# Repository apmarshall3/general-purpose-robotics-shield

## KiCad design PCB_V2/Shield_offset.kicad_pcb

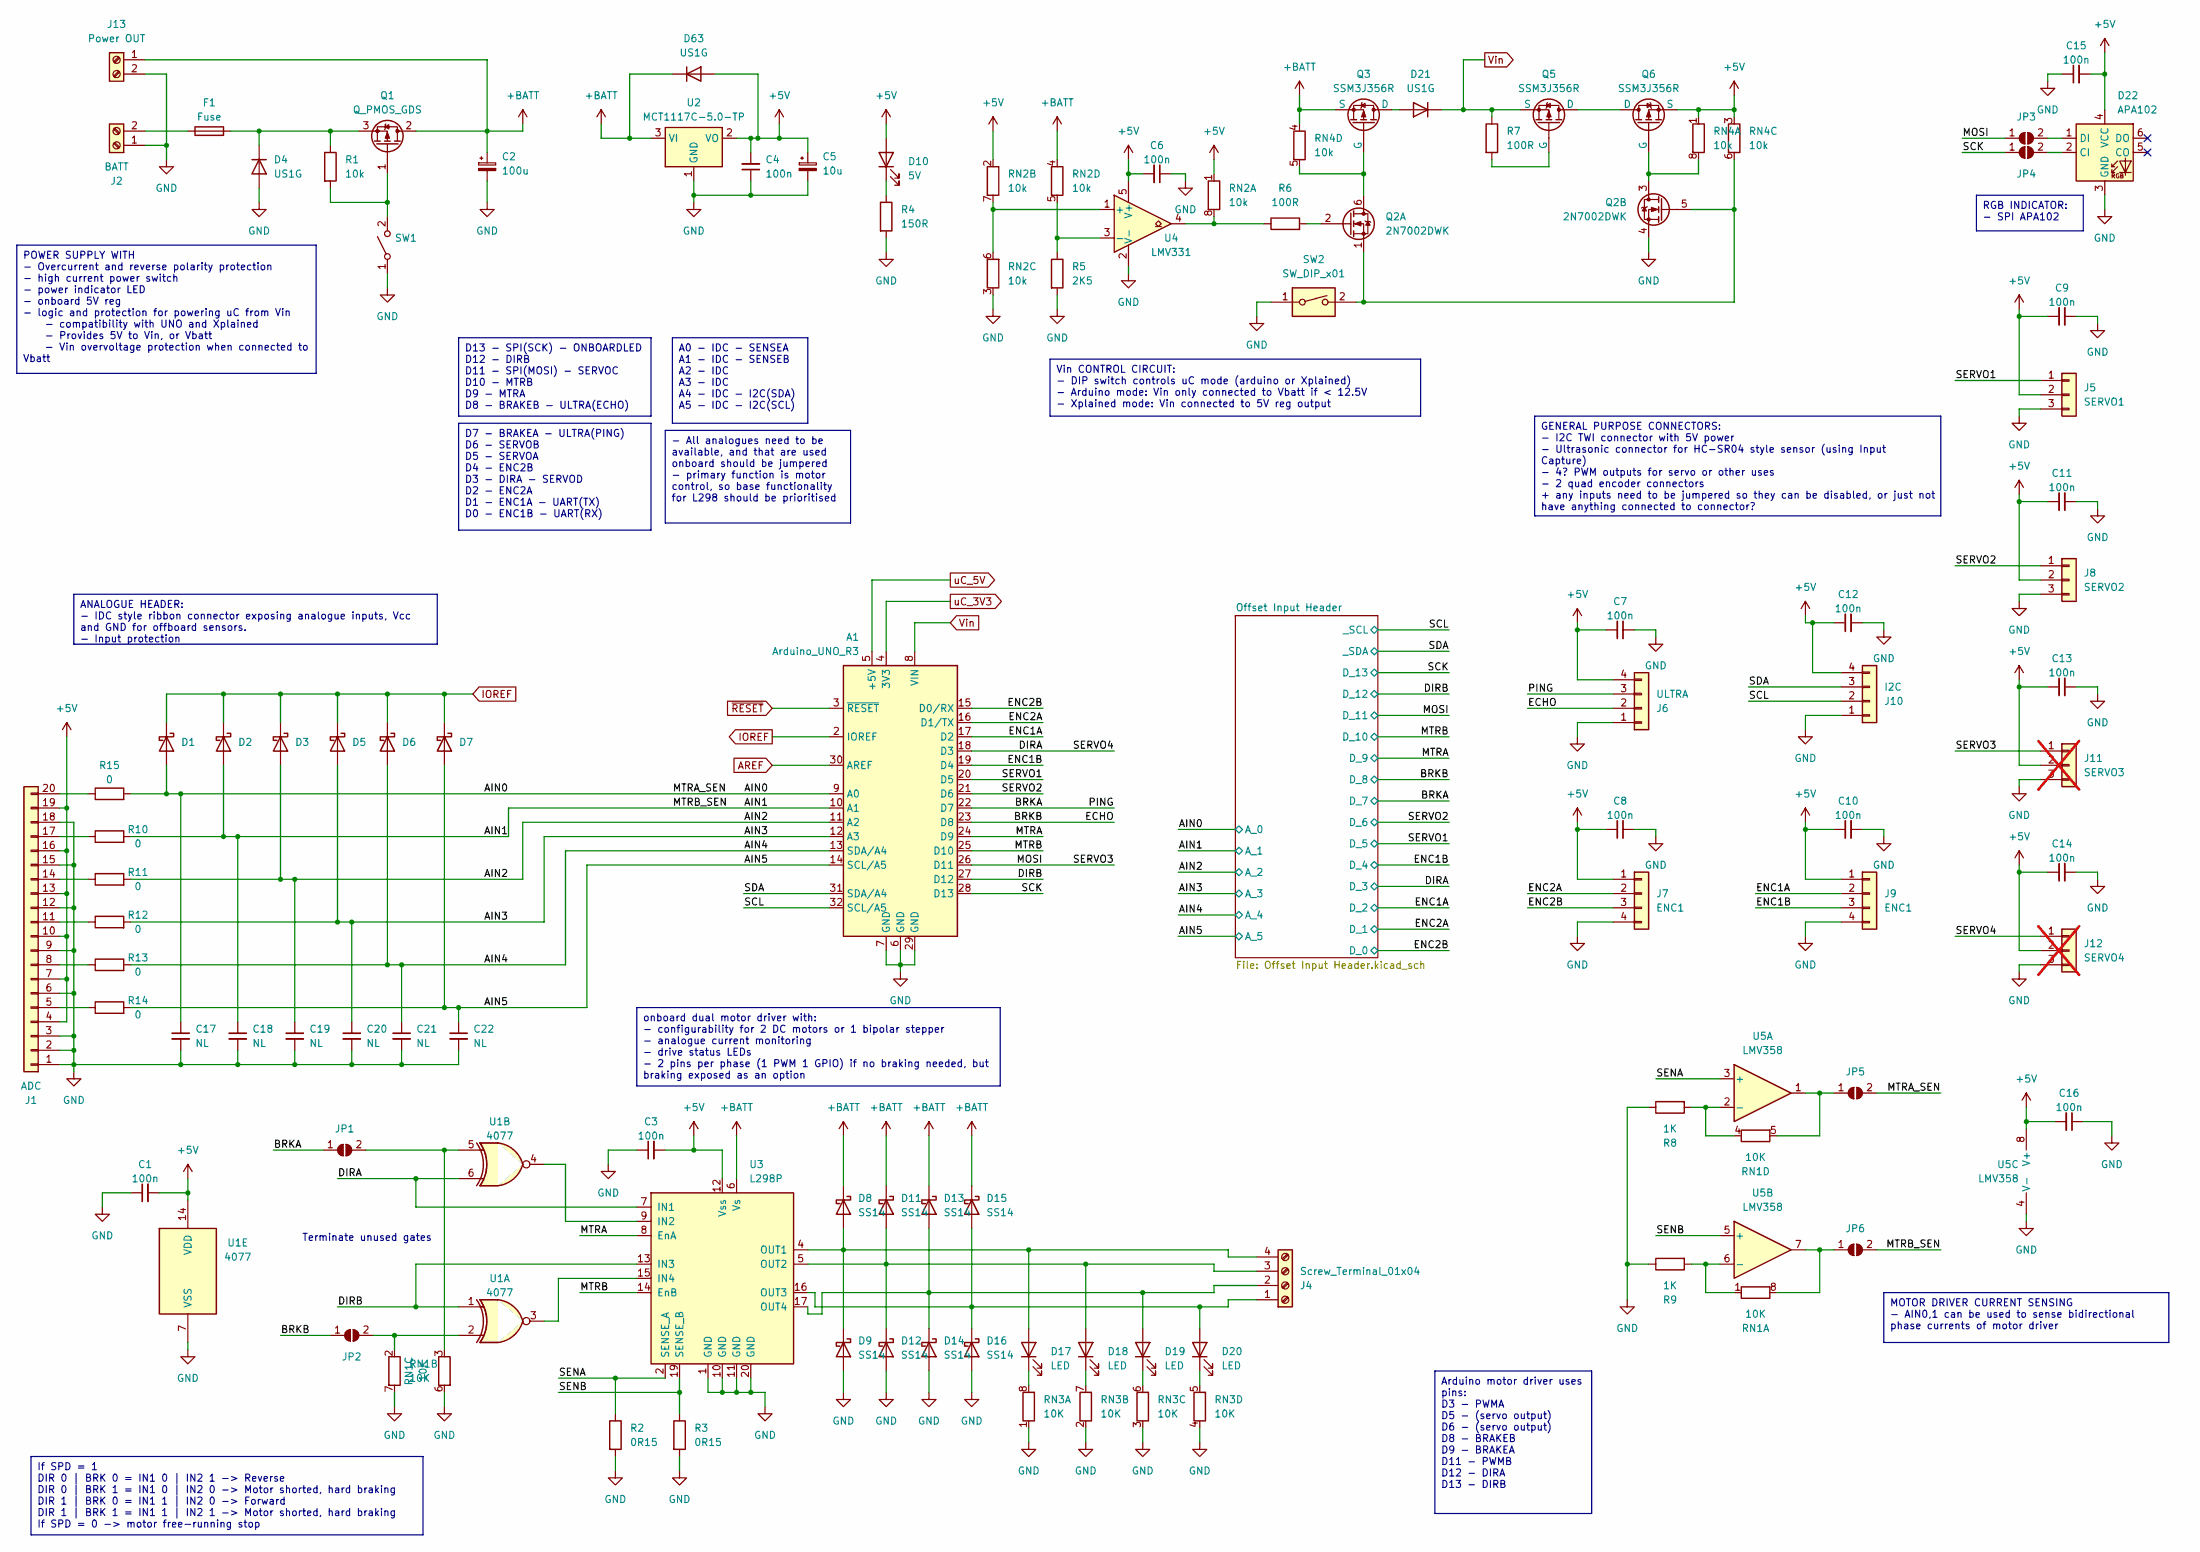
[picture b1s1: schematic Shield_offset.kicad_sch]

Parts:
A1: Arduino_UNO_R3
C1, C3, C4, C6, C7, C8, C9, C10, C11, C12, C13, C14, C15, C16: 100n; C_0805_2012Metric_Pad1.18x1.45mm_HandSolder
C2: 100u; CP_Elec_6.3x7.7; Manuf Part# HHXJ350ARA101MF80G
C5: 10u; CP_Elec_6.3x5.7
C17, C18, C19, C20, C21, C22: NL; C_0805_2012Metric_Pad1.18x1.45mm_HandSolder
D1, D2, D3, D5, D6, D7: CDBW140-G; D_SOD-123
D4, D21, D63: US1G; D_SMA
D8, D9, D11, D12, D13, D14, D15, D16: SS14; D_SMA
D10: 5V; LED_0805_2012Metric_Pad1.15x1.40mm_HandSolder
D17, D18, D19, D20: LED; LED_0805_2012Metric_Pad1.15x1.40mm_HandSolder
D22: APA102; LED_RGB_5050-6
F1: Fuse; Fuseholder_Clip-5x20mm_Littelfuse_445-030_Inline_P20.50x5.2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
J1: ADC; IDC-Header_2x10_P2.54mm_Vertical
J2: BATT; Amass_XT60PW-M_Kombifootprint
J4: Screw_Terminal_01x04; TerminalBlock_Phoenix_MKDS-1,5-4-5.08_1x04_P5.08mm_Horizont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
J5: SERVO1; PinHeader_1x03_P2.54mm_Vertical
J6: ULTRA; Molex_KK-254_1x04_P2.54mm_Horizontal
J7, J9: ENC1; Molex_KK-254_AE-6410-04A_1x04_P2.54mm_Vertical
J8: SERVO2; PinHeader_1x03_P2.54mm_Vertical
J10: I2C; Molex_KK-254_1x04_P2.54mm_Horizontal
J11: SERVO3; PinHeader_1x03_P2.54mm_Vertical; not fitted
J12: SERVO4; PinHeader_1x03_P2.54mm_Vertical; not fitted
J13: Power OUT; TerminalBlock_Phoenix_MKDS-1,5-2-5.08_1x02_P5.08mm_Horizont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
JP1, JP2, JP3, JP4, JP5, JP6: SolderJumper_2_Open; SolderJumper-2_P1.3mm_Open_RoundedPad1.0x1.5mm
Q1: Q_PMOS_GDS; SOT-223-3_TabPin2
Q2: 2N7002DWK; SOT-363_SC-70-6_Handsoldering
Q3, Q5, Q6: SSM3J356R; SOT-23-3
R1: 10k; R_0805_2012Metric_Pad1.20x1.40mm_HandSolder
R2, R3: 0R15; R_1206_3216Metric_Pad1.30x1.75mm_HandSolder
R4: 150R; R_0805_2012Metric_Pad1.20x1.40mm_HandSolder
R5: 2K5; R_0805_2012Metric_Pad1.20x1.40mm_HandSolder
R6, R7: 100R; R_0805_2012Metric_Pad1.20x1.40mm_HandSolder
R8, R9: 1K; R_0805_2012Metric_Pad1.20x1.40mm_HandSolder
R10, R11, R12, R13, R14, R15: 0; R_0603_1608Metric
RN1, RN3: 10K; R_Array_Convex_4x0603
RN2, RN4: 10k; R_Array_Convex_4x0603
SW1: PWR SW; SW_E-Switch_EG2219_DPDT_Angled
SW2: SW_DIP_x01; SW_DIP_SPSTx01_Slide_9.78x4.72mm_W8.61mm_P2.54mm
U1: 4077; SOIC-14_3.9x8.7mm_P1.27mm
U2: MCT1117C-5.0-TP; SOT-223-3_TabPin2
U3: L298P; SOIC127P1420X360-21N
U4: LMV331; SOT-353_SC-70-5
U5: LMV358; SOIC-8_3.9x4.9mm_P1.27mm

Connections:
+5V: C1.2, C3.2, C4.2, C5.1, C6.2, C7.1, C8.1, C9.1, C10.1, C11.1, C12.1, C13.1, C14.1, C15.2, C16.2, D10.2 (A), D22.4 (VCC), D63.2 (A), J1.4, J1.7, J1.10, J1.13, J1.16, J1.19, J5.2, J6.4, J7.1, J8.2, J9.1, J10.4, J11.2, J12.2, Q6.2 (S), RN2.1 (R1.1), RN2.2 (R2.1), RN4.1 (R1.1), RN4.3 (R3.1), U1.14 (VDD), U2.2 (VO), U3.12 (Vss), U4.5 (V+), U5.8 (V+)
+BATT: C2.1, D8.1 (K), D11.1 (K), D13.1 (K), D15.1 (K), D63.1 (K), J13.1, Q1.2 (D), Q3.2 (S), RN2.4 (R4.1), RN4.4 (R4.1), U2.3 (VI), U3.6 (Vs)
/AIN0: A1.9 (A0), C17.1, D1.2 (A), JP5.2 (B), R15.2; also elsewhere on the board
/AIN1: A1.10 (A1), C18.1, D2.2 (A), JP6.2 (B), R10.2; also elsewhere on the board
/AIN2: A1.11 (A2), C19.1, D3.2 (A), R11.2; also elsewhere on the board
/AIN3: A1.12 (A3), C20.1, D5.2 (A), R12.2; also elsewhere on the board
/AIN4: A1.13 (SDA/A4), C21.1, D6.2 (A), R13.2; also elsewhere on the board
/AIN5: A1.14 (SCL/A5), C22.1, D7.2 (A), R14.2; also elsewhere on the board
/BRKA: A1.22 (D7), J6.3, JP1.1 (A); also elsewhere on the board
/BRKB: A1.23 (D8), J6.2, JP2.1 (A); also elsewhere on the board
/DIRA: A1.18 (D3), J12.1, U1.6, U3.7 (IN1); also elsewhere on the board
/DIRB: A1.27 (D12), U1.1, U3.13 (IN3); also elsewhere on the board
/ENC1A: A1.17 (D2), J9.2; also elsewhere on the board
/ENC1B: A1.19 (D4), J9.3; also elsewhere on the board
/ENC2A: A1.16 (D1/TX), J7.2; also elsewhere on the board
/ENC2B: A1.15 (D0/RX), J7.3; also elsewhere on the board
/MOSI: A1.26 (D11), J11.1, JP3.1 (A); also elsewhere on the board
/MTRA: A1.24 (D9), U3.8 (EnA); also elsewhere on the board
/MTRB: A1.25 (D10), U3.14 (EnB); also elsewhere on the board
/SCK: A1.28 (D13), JP4.1 (A); also elsewhere on the board
/SCL: A1.32 (SCL/A5), J10.2; also elsewhere on the board
/SDA: A1.31 (SDA/A4), J10.3; also elsewhere on the board
/SENA: R2.1, U3.2 (SENSE_A), U5.3 (+)
/SENB: R3.1, U3.19 (SENSE_B), U5.5 (+)
/SERVO1: A1.20 (D5), J5.1; also elsewhere on the board
/SERVO2: A1.21 (D6), J8.1; also elsewhere on the board
AREF: A1.30 (AREF); also elsewhere on the board
GND: A1.6 (GND), A1.7 (GND), A1.29 (GND), C1.1, C2.2, C3.1, C4.1, C5.2, C6.1, C7.2, C8.2, C9.2, C10.2, C11.2, C12.2, C13.2, C14.2, C15.1, C16.1, C17.2, C18.2, C19.2, C20.2, C21.2, C22.2, D4.2 (A), D9.2 (A), D12.2 (A), D14.2 (A), D16.2 (A), D22.3 (GND), J1.1, J1.2, J1.3, J1.6, J1.9, J1.12, J1.15, J1.18, J2.1, J5.3, J6.1, J7.4, J8.3, J9.4, J10.1, J11.3, J12.3, J13.2, Q2.4 (S), R2.2, R3.2, R4.2, R5.2, R8.1, R9.1, RN1.6 (R3.2), RN1.7 (R2.2), RN2.3 (R3.1), RN3.1 (R1.1), RN3.2 (R2.1), RN3.3 (R3.1), RN3.4 (R4.1), SW1.1 (A), SW2.1, U1.7 (VSS), U2.1 (GND), U3.1 (GND), U3.10 (GND), U3.11 (GND), U3.20 (GND), U4.2 (V-), U5.4 (V-); also elsewhere on the board
IOREF: A1.2 (IOREF), D1.1 (K), D2.1 (K), D3.1 (K), D5.1 (K), D6.1 (K), D7.1 (K); also elsewhere on the board
unnamed: D4.1 (K), F1.2, Q1.3 (S), R1.1
unnamed: D10.1 (K), R4.1
unnamed: D11.2 (A), D12.1 (K), D18.2 (A), J4.3, U3.5 (OUT2)
unnamed: D13.2 (A), D14.1 (K), D19.2 (A), J4.2, U3.17 (OUT4)
unnamed: D15.2 (A), D16.1 (K), D20.2 (A), J4.1, U3.16 (OUT3)
unnamed: D8.2 (A), D9.1 (K), D17.2 (A), J4.4, U3.4 (OUT1)
unnamed: D17.1 (K), RN3.8 (R1.2)
unnamed: D18.1 (K), RN3.7 (R2.2)
unnamed: D19.1 (K), RN3.6 (R3.2)
unnamed: D20.1 (K), RN3.5 (R4.2)
unnamed: D21.2 (A), Q3.3 (D)
unnamed: D22.2 (CI), JP4.2 (B)
unnamed: D22.1 (DI), JP3.2 (B)
unnamed: J1.5, R14.1
unnamed: J1.8, R13.1
unnamed: J1.11, R12.1
unnamed: J1.14, R11.1
unnamed: J1.17, R10.1
unnamed: J1.20, R15.1
unnamed: F1.1, J2.2
unnamed: JP1.2 (B), RN1.3 (R3.1), U1.5
unnamed: JP2.2 (B), RN1.2 (R2.1), U1.2
unnamed: JP5.1 (A), RN1.5 (R4.2), U5.1
unnamed: JP6.1 (A), RN1.8 (R1.2), U5.7
unnamed: Q1.1 (G), R1.2, SW1.2 (B)
unnamed: Q2.6 (D), Q3.1 (G), RN4.5 (R4.2)
unnamed: Q2.2 (G), R6.2
unnamed: Q2.1 (S), Q2.5 (G), RN4.6 (R3.2), SW2.2
unnamed: Q2.3 (D), Q6.1 (G), RN4.8 (R1.2)
unnamed: Q5.3 (D), Q6.3 (D)
unnamed: Q5.1 (G), R7.2
unnamed: R9.2, RN1.1 (R1.1), U5.6 (-)
unnamed: R8.2, RN1.4 (R4.1), U5.2 (-)
unnamed: R6.1, RN2.8 (R1.2), U4.4
unnamed: RN2.6 (R3.2), RN2.7 (R2.2), U4.1 (+)
unnamed: R5.1, RN2.5 (R4.2), U4.3 (-)
unnamed: U1.4, U3.9 (IN2)
unnamed: U1.3, U3.15 (IN4)
Vin: A1.8 (VIN), D21.1 (K), Q5.2 (S), R7.1; also elsewhere on the board
uC_3V3: A1.4 (3V3); also elsewhere on the board
uC_5V: A1.5 (+5V); also elsewhere on the board
~RESET: A1.3 (~RESET); also elsewhere on the board

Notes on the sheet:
D7 - BRAKEA - ULTRA(PING) D6 - SERVOB D5 - SERVOA D4 - ENC2B D3 - DIRA - SERVOD D2 - ENC2A D1 - ENC1A - UART(TX) D0 - ENC1B - UART(RX)
D13 - SPI(SCK) - ONBOARDLED D12 - DIRB D11 - SPI(MOSI) - SERVOC D10 - MTRB D9 - MTRA D8 - BRAKEB - ULTRA(ECHO)
RGB INDICATOR: - SPI APA102
Vin CONTROL CIRCUIT: - DIP switch controls uC mode (arduino or Xplained) - Arduino mode: Vin only connected to Vbatt if < 12.5V - Xplained mode: Vin connected to 5V reg output
Arduino motor driver uses pins: D3 - PWMA D5 - (servo output) D6 - (servo output) D8 - BRAKEB D9 - BRAKEA D11 - PWMB D12 - DIRA D13 - DIRB
- All analogues need to be available, and that are used onboard should be jumpered - primary function is motor control, so base functionality for L298 should be prioritised
POWER SUPPLY WITH - Overcurrent and reverse polarity protection - high current power switch - power indicator LED - onboard 5V reg - logic and protection for powering uC from Vin - compatibility with UNO and Xplained - Provides 5V to Vin, or Vbatt - Vin overvoltage protection when connected to Vbatt
A0 - IDC - SENSEA A1 - IDC - SENSEB A2 - IDC A3 - IDC A4 - IDC - I2C(SDA) A5 - IDC - I2C(SCL)
ANALOGUE HEADER: - IDC style ribbon connector exposing analogue inputs, Vcc and GND for offboard sensors. - Input protection
If SPD = 1 DIR 0 | BRK 0 = IN1 0 | IN2 1 -> Reverse DIR 0 | BRK 1 = IN1 0 | IN2 0 -> Motor shorted, hard braking DIR 1 | BRK 0 = IN1 1 | IN2 0 -> Forward DIR 1 | BRK 1 = IN1 1 | IN2 1 -> Motor shorted, hard braking If SPD = 0 -> motor free-running stop
onboard dual motor driver with: - configurability for 2 DC motors or 1 bipolar stepper - analogue current monitoring - drive status LEDs - 2 pins per phase (1 PWM 1 GPIO) if no braking needed, but braking exposed as an option
GENERAL PURPOSE CONNECTORS: - I2C TWI connector with 5V power - Ultrasonic connector for HC-SR04 style sensor (using Input Capture) - 4? PWM outputs for servo or other uses - 2 quad encoder connectors + any inputs need to be jumpered so they can be disabled, or just not have anything connected to c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
MOTOR DRIVER CURRENT SENSING - AIN0,1 can be used to sense bidirectional phase currents of motor driver
Terminate unused gates

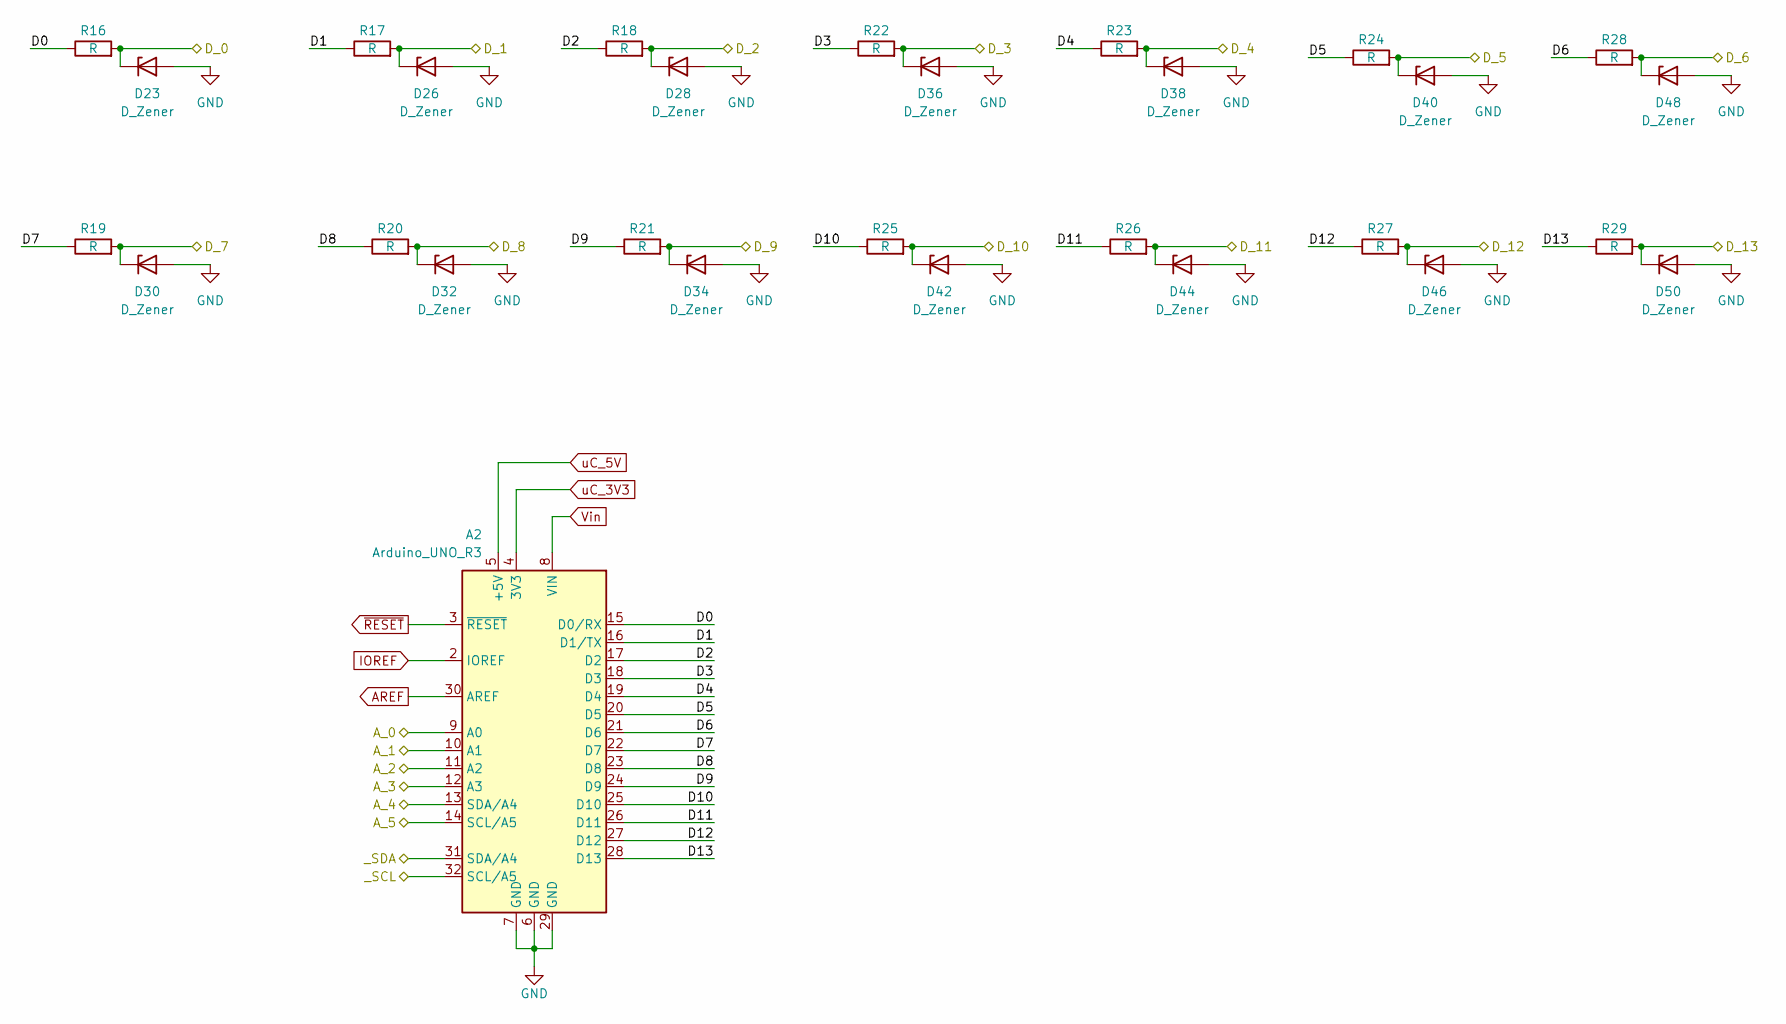
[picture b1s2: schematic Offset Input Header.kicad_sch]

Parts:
A2: Arduino_UNO_R3
D23, D26, D28, D30, D32, D34, D36, D38, D40, D42, D44, D46, D48, D50: D_Zener; D_SOD-123
R16, R17, R18, R19, R20, R21, R22, R23, R24, R25, R26, R27, R28, R29: R; R_0805_2012Metric

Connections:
/AIN0: A2.9 (A0); also elsewhere on the board
/AIN1: A2.10 (A1); also elsewhere on the board
/AIN2: A2.11 (A2); also elsewhere on the board
/AIN3: A2.12 (A3); also elsewhere on the board
/AIN4: A2.13 (SDA/A4); also elsewhere on the board
/AIN5: A2.14 (SCL/A5); also elsewhere on the board
/BRKA: D30.1 (K), R19.2; also elsewhere on the board
/BRKB: D32.1 (K), R20.2; also elsewhere on the board
/DIRA: D36.1 (K), R22.2; also elsewhere on the board
/DIRB: D46.1 (K), R27.2; also elsewhere on the board
/ENC1A: D28.1 (K), R18.2; also elsewhere on the board
/ENC1B: D38.1 (K), R23.2; also elsewhere on the board
/ENC2A: D26.1 (K), R17.2; also elsewhere on the board
/ENC2B: D23.1 (K), R16.2; also elsewhere on the board
/MOSI: D44.1 (K), R26.2; also elsewhere on the board
/MTRA: D34.1 (K), R21.2; also elsewhere on the board
/MTRB: D42.1 (K), R25.2; also elsewhere on the board
/Offset Input Header/D0: A2.15 (D0/RX), R16.1
/Offset Input Header/D1: A2.16 (D1/TX), R17.1
/Offset Input Header/D2: A2.17 (D2), R18.1
/Offset Input Header/D3: A2.18 (D3), R22.1
/Offset Input Header/D4: A2.19 (D4), R23.1
/Offset Input Header/D5: A2.20 (D5), R24.1
/Offset Input Header/D6: A2.21 (D6), R28.1
/Offset Input Header/D7: A2.22 (D7), R19.1
/Offset Input Header/D8: A2.23 (D8), R20.1
/Offset Input Header/D9: A2.24 (D9), R21.1
/Offset Input Header/D10: A2.25 (D10), R25.1
/Offset Input Header/D11: A2.26 (D11), R26.1
/Offset Input Header/D12: A2.27 (D12), R27.1
/Offset Input Header/D13: A2.28 (D13), R29.1
/SCK: D50.1 (K), R29.2; also elsewhere on the board
/SCL: A2.32 (SCL/A5); also elsewhere on the board
/SDA: A2.31 (SDA/A4); also elsewhere on the board
/SERVO1: D40.1 (K), R24.2; also elsewhere on the board
/SERVO2: D48.1 (K), R28.2; also elsewhere on the board
AREF: A2.30 (AREF); also elsewhere on the board
GND: A2.6 (GND), A2.7 (GND), A2.29 (GND), D23.2 (A), D26.2 (A), D28.2 (A), D30.2 (A), D32.2 (A), D34.2 (A), D36.2 (A), D38.2 (A), D40.2 (A), D42.2 (A), D44.2 (A), D46.2 (A), D48.2 (A), D50.2 (A); also elsewhere on the board
IOREF: A2.2 (IOREF); also elsewhere on the board
Vin: A2.8 (VIN); also elsewhere on the board
uC_3V3: A2.4 (3V3); also elsewhere on the board
uC_5V: A2.5 (+5V); also elsewhere on the board
~RESET: A2.3 (~RESET); also elsewhere on the board

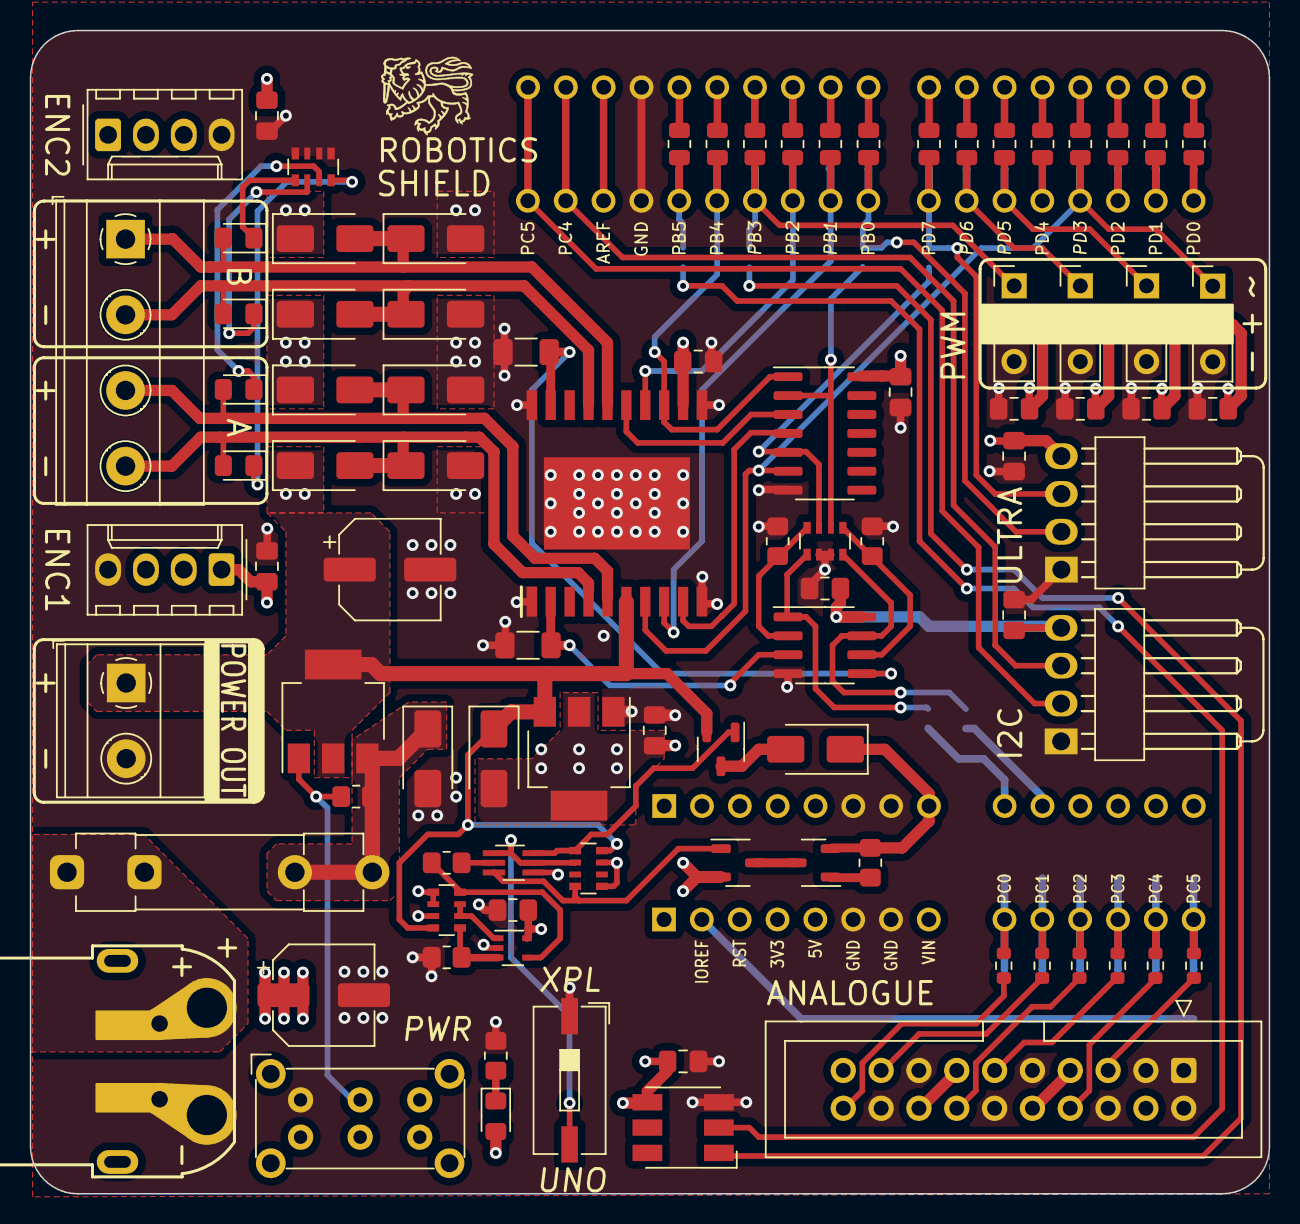
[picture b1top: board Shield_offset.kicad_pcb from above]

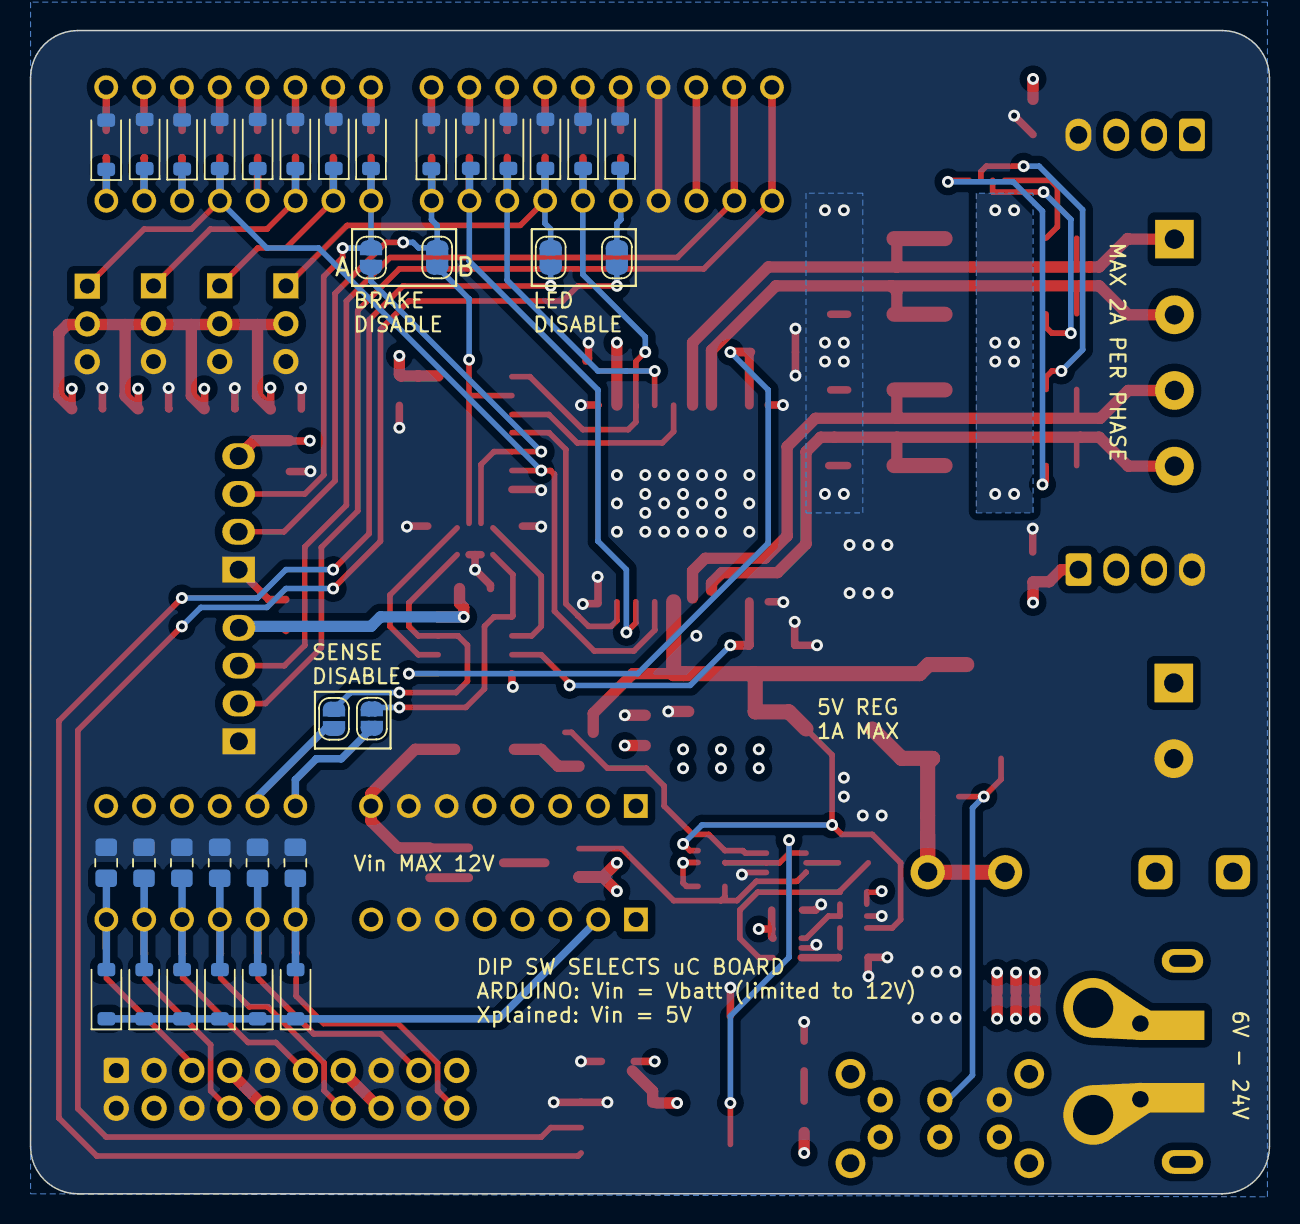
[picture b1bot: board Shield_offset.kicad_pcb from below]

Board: 4 copper layers, 83.2 x 78.1 mm, 125 parts (34 on the bottom side), 85 nets.

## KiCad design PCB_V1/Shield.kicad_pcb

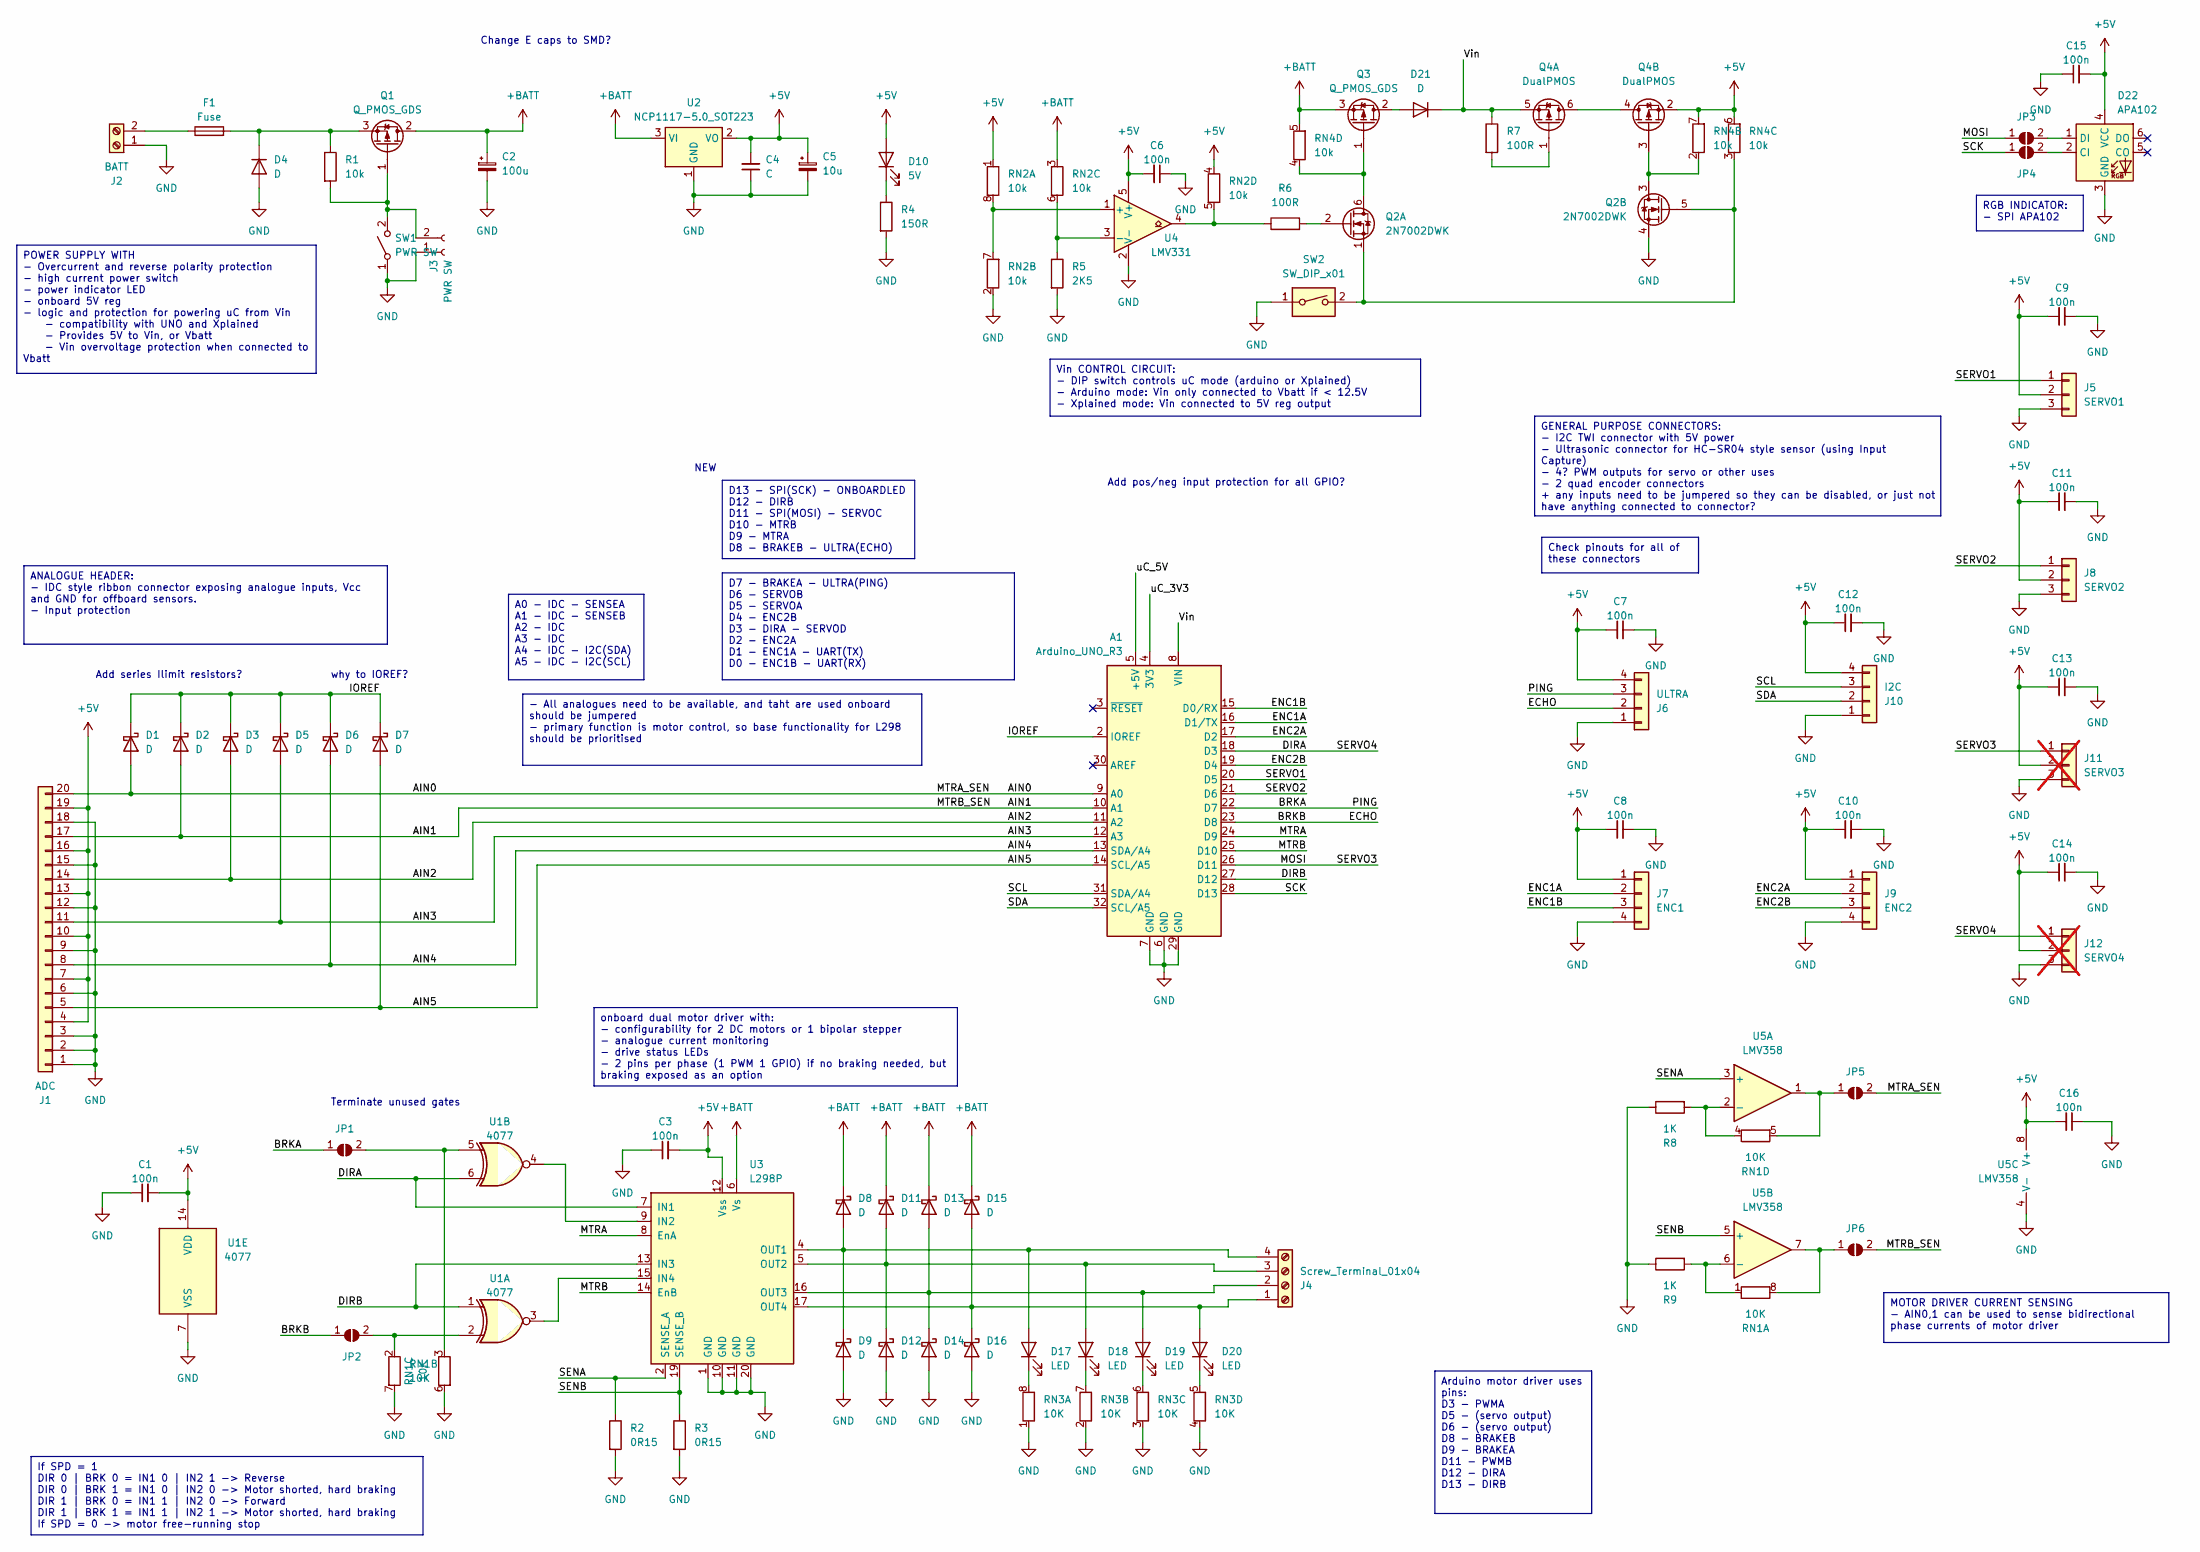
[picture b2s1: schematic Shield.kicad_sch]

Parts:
A1: Arduino_UNO_R3
C1, C3, C6, C7, C8, C9, C10, C11, C12, C13, C14, C15, C16: 100n; C_0805_2012Metric_Pad1.18x1.45mm_HandSolder
C2: 100u; CP_Radial_D5.0mm_P2.50mm
C4: C; C_0805_2012Metric_Pad1.18x1.45mm_HandSolder
C5: 10u; CP_Radial_D5.0mm_P2.50mm
D1, D2, D3, D4, D5, D6, D7, D8, D9, D11, D12, D13, D14, D15, D16, D21: D; D_SOD-123
D10: 5V; LED_0805_2012Metric_Pad1.15x1.40mm_HandSolder
D17, D18, D19, D20: LED; LED_0805_2012Metric_Pad1.15x1.40mm_HandSolder
D22: APA102; LED_RGB_5050-6
F1: Fuse; Fuseholder_Clip-5x20mm_Littelfuse_445-030_Inline_P20.50x5.2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
J1: ADC; IDC-Header_2x10_P2.54mm_Horizontal
J2: BATT; Amass_XT60PW-M_Kombifootprint
J3: PWR SW; PinHeader_1x02_P2.54mm_Vertical
J4: Screw_Terminal_01x04; TerminalBlock_bornier-4_P5.08mm
J5: SERVO1; PinHeader_1x03_P2.54mm_Vertical
J6: ULTRA; Molex_KK-254_1x04_P2.54mm_Horizontal
J7: ENC1; Molex_KK-254_AE-6410-04A_1x04_P2.54mm_Vertical
J8: SERVO2; PinHeader_1x03_P2.54mm_Vertical
J9: ENC2; Molex_KK-254_AE-6410-04A_1x04_P2.54mm_Vertical
J10: I2C; Molex_KK-254_1x04_P2.54mm_Horizontal
J11: SERVO3; PinHeader_1x03_P2.54mm_Vertical; not fitted
J12: SERVO4; PinHeader_1x03_P2.54mm_Vertical; not fitted
JP1, JP2, JP3, JP4, JP5, JP6: SolderJumper_2_Open; SolderJumper-2_P1.3mm_Open_RoundedPad1.0x1.5mm
Q1: Q_PMOS_GDS; SOT-223-3_TabPin2
Q2: 2N7002DWK; SOT-363_SC-70-6_Handsoldering
Q3: Q_PMOS_GDS; SOT-323_SC-70_Handsoldering
Q4: DualPMOS; SOT-23-6_Handsoldering
R1: 10k; R_0805_2012Metric_Pad1.20x1.40mm_HandSolder
R2, R3: 0R15; R_1206_3216Metric_Pad1.30x1.75mm_HandSolder
R4: 150R; R_0805_2012Metric_Pad1.20x1.40mm_HandSolder
R5: 2K5; R_0805_2012Metric_Pad1.20x1.40mm_HandSolder
R6, R7: 100R; R_0805_2012Metric_Pad1.20x1.40mm_HandSolder
R8, R9: 1K; R_0805_2012Metric_Pad1.20x1.40mm_HandSolder
RN1, RN3: 10K; R_Array_Convex_4x0603
RN2, RN4: 10k; R_Array_Convex_4x0603
SW1: PWR SW; SW_E-Switch_EG2219_DPDT_Angled
SW2: SW_DIP_x01; SW_DIP_SPSTx01_Slide_9.78x4.72mm_W8.61mm_P2.54mm
U1: 4077; SOIC-14_3.9x8.7mm_P1.27mm
U2: NCP1117-5.0_SOT223; SOT-223-3_TabPin2
U3: L298P; SOIC127P1420X360-21N
U4: LMV331; SOT-23-5
U5: LMV358; SOIC-8_3.9x4.9mm_P1.27mm

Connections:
+5V: C1.2, C3.2, C4.2, C5.1, C6.2, C7.1, C8.1, C9.1, C10.1, C11.1, C12.1, C13.1, C14.1, C15.2, C16.2, D10.2 (A), D22.4 (VCC), J1.4, J1.7, J1.10, J1.13, J1.16, J1.19, J5.2, J6.4, J7.1, J8.2, J9.1, J10.4, J11.2, J12.2, Q4.2 (S), RN2.1 (R1.1), RN2.4 (R4.1), RN4.6 (R3.2), RN4.7 (R2.2), U1.14 (VDD), U2.2 (VO), U3.12 (Vss), U4.5 (V+), U5.8 (V+)
+BATT: C2.1, D8.1 (K), D11.1 (K), D13.1 (K), D15.1 (K), Q1.2 (D), Q3.3 (S), RN2.3 (R3.1), RN4.5 (R4.2), U2.3 (VI), U3.6 (Vs)
/AIN0: A1.9 (A0), D1.2 (A), J1.20, JP5.2 (B)
/AIN1: A1.10 (A1), D2.2 (A), J1.17, JP6.2 (B)
/AIN2: A1.11 (A2), D3.2 (A), J1.14
/AIN3: A1.12 (A3), D5.2 (A), J1.11
/AIN4: A1.13 (SDA/A4), D6.2 (A), J1.8
/AIN5: A1.14 (SCL/A5), D7.2 (A), J1.5
/BRKA: A1.22 (D7), J6.3, JP1.1 (A)
/BRKB: A1.23 (D8), J6.2, JP2.1 (A)
/DIRA: A1.18 (D3), J12.1, U1.6, U3.7 (IN1)
/DIRB: A1.27 (D12), U1.1, U3.13 (IN3)
/ENC1A: A1.16 (D1/TX), J7.2
/ENC1B: A1.15 (D0/RX), J7.3
/ENC2A: A1.17 (D2), J9.2
/ENC2B: A1.19 (D4), J9.3
/IOREF: A1.2 (IOREF), D1.1 (K), D2.1 (K), D3.1 (K), D5.1 (K), D6.1 (K), D7.1 (K)
/MOSI: A1.26 (D11), J11.1, JP3.1 (A)
/MTRA: A1.24 (D9), U3.8 (EnA)
/MTRB: A1.25 (D10), U3.14 (EnB)
/SCK: A1.28 (D13), JP4.1 (A)
/SCL: A1.31 (SDA/A4), J10.3
/SDA: A1.32 (SCL/A5), J10.2
/SENA: R2.1, U3.2 (SENSE_A), U5.3 (+)
/SENB: R3.1, U3.19 (SENSE_B), U5.5 (+)
/SERVO1: A1.20 (D5), J5.1
/SERVO2: A1.21 (D6), J8.1
/Vin: A1.8 (VIN), D21.1 (K), Q4.5 (S), R7.1
/uC_3V3: A1.4 (3V3)
/uC_5V: A1.5 (+5V)
GND: A1.6 (GND), A1.7 (GND), A1.29 (GND), C1.1, C2.2, C3.1, C4.1, C5.2, C6.1, C7.2, C8.2, C9.2, C10.2, C11.2, C12.2, C13.2, C14.2, C15.1, C16.1, D4.2 (A), D9.2 (A), D12.2 (A), D14.2 (A), D16.2 (A), D22.3 (GND), J1.1, J1.2, J1.3, J1.6, J1.9, J1.12, J1.15, J1.18, J2.1, J3.1, J5.3, J6.1, J7.4, J8.3, J9.4, J10.1, J11.3, J12.3, Q2.4 (S), R2.2, R3.2, R4.2, R5.2, R8.1, R9.1, RN1.6 (R3.2), RN1.7 (R2.2), RN2.2 (R2.1), RN3.1 (R1.1), RN3.2 (R2.1), RN3.3 (R3.1), RN3.4 (R4.1), SW1.1 (A), SW2.1, U1.7 (VSS), U2.1 (GND), U3.1 (GND), U3.10 (GND), U3.11 (GND), U3.20 (GND), U4.2 (V-), U5.4 (V-)
unnamed: D4.1 (K), F1.2, Q1.3 (S), R1.1
unnamed: D10.1 (K), R4.1
unnamed: D11.2 (A), D12.1 (K), D18.2 (A), J4.3, U3.5 (OUT2)
unnamed: D13.2 (A), D14.1 (K), D19.2 (A), J4.2, U3.16 (OUT3)
unnamed: D15.2 (A), D16.1 (K), D20.2 (A), J4.1, U3.17 (OUT4)
unnamed: D8.2 (A), D9.1 (K), D17.2 (A), J4.4, U3.4 (OUT1)
unnamed: D17.1 (K), RN3.8 (R1.2)
unnamed: D18.1 (K), RN3.7 (R2.2)
unnamed: D19.1 (K), RN3.6 (R3.2)
unnamed: D20.1 (K), RN3.5 (R4.2)
unnamed: D21.2 (A), Q3.2 (D)
unnamed: D22.2 (CI), JP4.2 (B)
unnamed: D22.1 (DI), JP3.2 (B)
unnamed: F1.1, J2.2
unnamed: J3.2, Q1.1 (G), R1.2, SW1.2 (B)
unnamed: JP1.2 (B), RN1.3 (R3.1), U1.5
unnamed: JP2.2 (B), RN1.2 (R2.1), U1.2
unnamed: JP5.1 (A), RN1.5 (R4.2), U5.1
unnamed: JP6.1 (A), RN1.8 (R1.2), U5.7
unnamed: Q2.6 (D), Q3.1 (G), RN4.4 (R4.1)
unnamed: Q2.2 (G), R6.2
unnamed: Q2.1 (S), Q2.5 (G), RN4.3 (R3.1), SW2.2
unnamed: Q2.3 (D), Q4.3 (G), RN4.2 (R2.1)
unnamed: Q4.4 (D), Q4.6 (D)
unnamed: Q4.1 (G), R7.2
unnamed: R9.2, RN1.1 (R1.1), U5.6 (-)
unnamed: R8.2, RN1.4 (R4.1), U5.2 (-)
unnamed: RN2.7 (R2.2), RN2.8 (R1.2), U4.1 (+)
unnamed: R5.1, RN2.6 (R3.2), U4.3 (-)
unnamed: R6.1, RN2.5 (R4.2), U4.4
unnamed: U1.4, U3.9 (IN2)
unnamed: U1.3, U3.15 (IN4)

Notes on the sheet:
D7 - BRAKEA - ULTRA(PING) D6 - SERVOB D5 - SERVOA D4 - ENC2B D3 - DIRA - SERVOD D2 - ENC2A D1 - ENC1A - UART(TX) D0 - ENC1B - UART(RX)
D13 - SPI(SCK) - ONBOARDLED D12 - DIRB D11 - SPI(MOSI) - SERVOC D10 - MTRB D9 - MTRA D8 - BRAKEB - ULTRA(ECHO)
RGB INDICATOR: - SPI APA102
Vin CONTROL CIRCUIT: - DIP switch controls uC mode (arduino or Xplained) - Arduino mode: Vin only connected to Vbatt if < 12.5V - Xplained mode: Vin connected to 5V reg output
Check pinouts for all of these connectors
Arduino motor driver uses pins: D3 - PWMA D5 - (servo output) D6 - (servo output) D8 - BRAKEB D9 - BRAKEA D11 - PWMB D12 - DIRA D13 - DIRB
- All analogues need to be available, and taht are used onboard should be jumpered - primary function is motor control, so base functionality for L298 should be prioritised
POWER SUPPLY WITH - Overcurrent and reverse polarity protection - high current power switch - power indicator LED - onboard 5V reg - logic and protection for powering uC from Vin - compatibility with UNO and Xplained - Provides 5V to Vin, or Vbatt - Vin overvoltage protection when connected to Vbatt
A0 - IDC - SENSEA A1 - IDC - SENSEB A2 - IDC A3 - IDC A4 - IDC - I2C(SDA) A5 - IDC - I2C(SCL)
ANALOGUE HEADER: - IDC style ribbon connector exposing analogue inputs, Vcc and GND for offboard sensors. - Input protection
If SPD = 1 DIR 0 | BRK 0 = IN1 0 | IN2 1 -> Reverse DIR 0 | BRK 1 = IN1 0 | IN2 0 -> Motor shorted, hard braking DIR 1 | BRK 0 = IN1 1 | IN2 0 -> Forward DIR 1 | BRK 1 = IN1 1 | IN2 1 -> Motor shorted, hard braking If SPD = 0 -> motor free-running stop
onboard dual motor driver with: - configurability for 2 DC motors or 1 bipolar stepper - analogue current monitoring - drive status LEDs - 2 pins per phase (1 PWM 1 GPIO) if no braking needed, but braking exposed as an option
GENERAL PURPOSE CONNECTORS: - I2C TWI connector with 5V power - Ultrasonic connector for HC-SR04 style sensor (using Input Capture) - 4? PWM outputs for servo or other uses - 2 quad encoder connectors + any inputs need to be jumpered so they can be disabled, or just not have anything connected to c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
MOTOR DRIVER CURRENT SENSING - AIN0,1 can be used to sense bidirectional phase currents of motor driver
Add series Ilimit resistors?
why to IOREF?
NEW
Terminate unused gates
Add pos/neg input protection for all GPIO?
Change E caps to SMD?
